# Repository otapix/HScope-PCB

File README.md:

# HScope-PCB
HScope PCB

PCB for 

https://www.martinloren.com/

https://github.com/martinloren/HScope/

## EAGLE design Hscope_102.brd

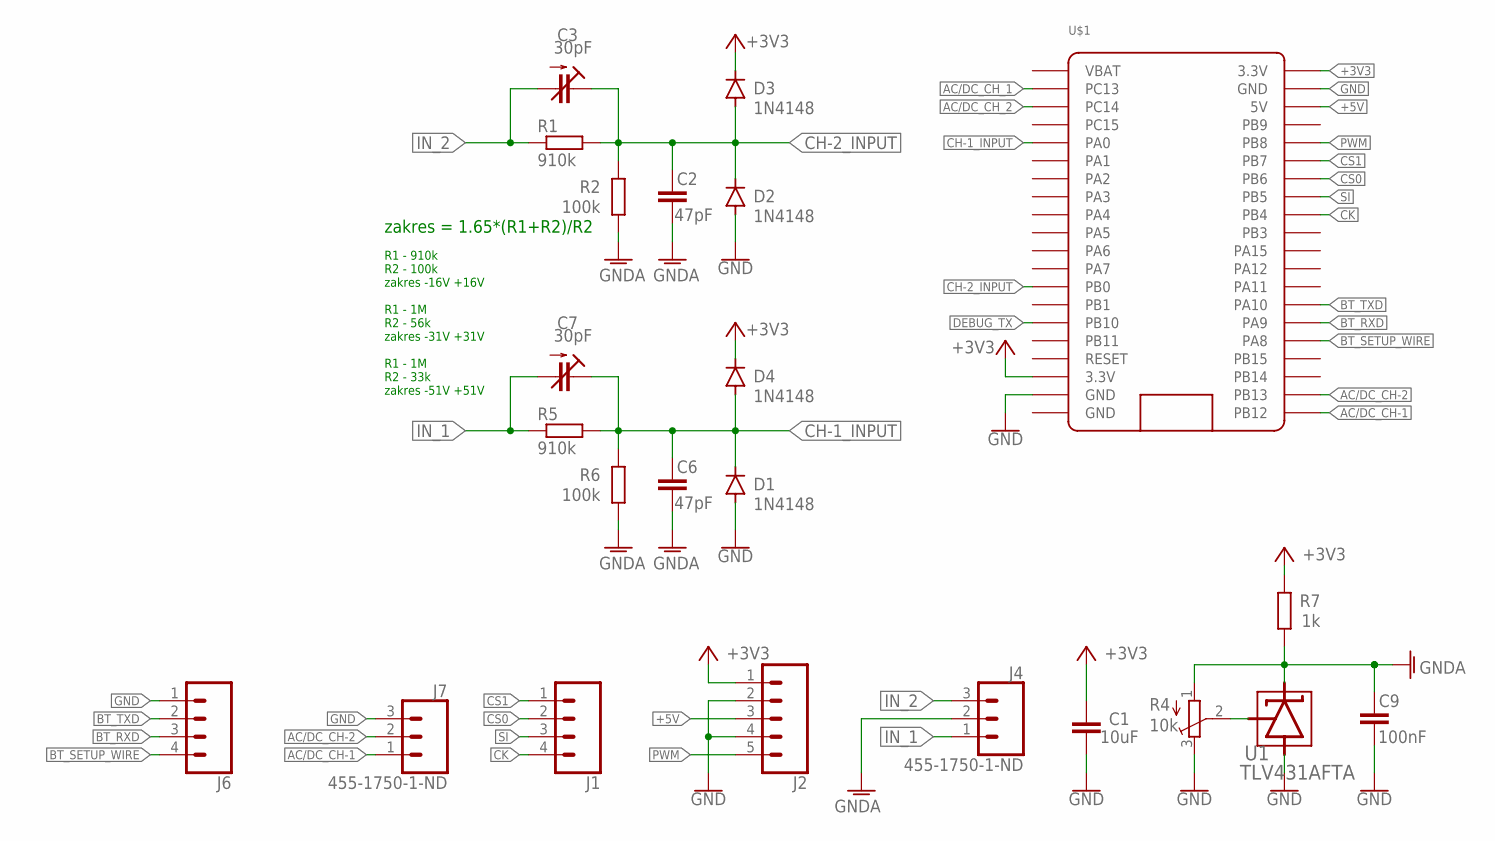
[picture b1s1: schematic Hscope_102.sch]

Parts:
C1: 10uF; C0805
C2, C6: 47pF; C0805
C3, C7: 30pF; CTRIM3018_12
C9: 100nF; C0805
D1, D2, D3, D4: 1N4148; SOD323-W
J1, J6: CONN_04PTH; 1X04
J2: CONN_05; 1X05
J4, J7: 455-1750-1-ND; 1X03
R1, R5: 910k; R0805
R2, R6: 100k; R0805
R4: 10k; SM-42/43A
R7: 1k; R0805
U1: TLV431AFTA; SOT95P237X112-3N
U$1: STM32_BLUEPILL

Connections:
+3V3: C1.2, D3.C, D4.C, J2.1, R7.2, U$1.P$20 (3.3V), U$1.P$23 (3.3V)
+5V: J2.3, U$1.P$18 (5V)
AC/DC_CH-1: J7.1, U$1.P$1 (PB12)
AC/DC_CH-2: J7.2, U$1.P$2 (PB13)
AC/DC_CH_1: U$1.P$39 (PC13)
AC/DC_CH_2: U$1.P$38 (PC14)
BT_RXD: J6.3, U$1.P$6 (PA9)
BT_SETUP_WIRE: J6.4, U$1.P$5 (PA8)
BT_TXD: J6.2, U$1.P$7 (PA10)
CH-1_INPUT: C6.2, C7.+ (E), D1.C, D4.A, R5.2, R6.2, U$1.P$36 (PA0)
CH-2_INPUT: C2.2, C3.+ (E), D2.C, D3.A, R1.2, R2.2, U$1.P$28 (PB0)
CK: J1.4, U$1.P$12 (PB4)
CS0: J1.2, U$1.P$14 (PB6)
CS1: J1.1, U$1.P$15 (PB7)
DEBUG_TX: U$1.P$26 (PB10)
GND: C1.1, C9.1, D1.A, D2.A, J2.2, J2.4, J6.1, J7.3, R4.3 (E), U1.3 (ANODE), U$1.P$19 (GND), U$1.P$21 (GND), U$1.P$22 (GND)
GNDA: C2.1, C6.1, C9.2, J4.2, R2.1, R4.1 (A), R6.1, R7.1, U1.2 (CATHODE)
IN_1: C7.- (A), J4.1, R5.1
IN_2: C3.- (A), J4.3, R1.1
unnamed: R4.2 (S), U1.1 (REF)
PWM: J2.5, U$1.P$16 (PB8)
SI: J1.3, U$1.P$13 (PB5)
VBAT: U$1.P$40 (VBAT)

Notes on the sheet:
R1 - 910k R2 - 100k zakres -16V +16V R1 - 1M R2 - 56k zakres -31V +31V R1 - 1M R2 - 33k zakres -51V +51V
zakres = 1.65*(R1+R2)/R2

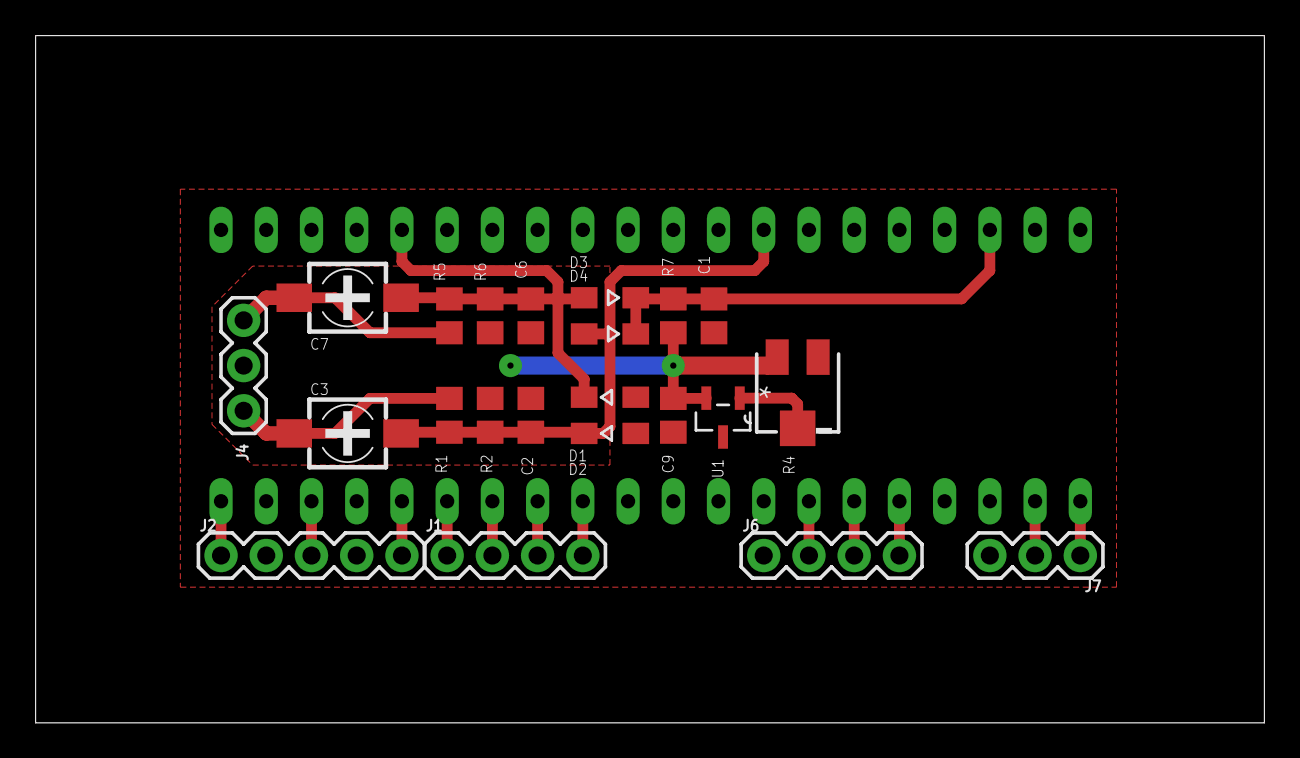
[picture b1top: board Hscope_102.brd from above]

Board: 2 copper layers, 69.0 x 38.6 mm, 23 parts (1 on the bottom side), 19 nets.

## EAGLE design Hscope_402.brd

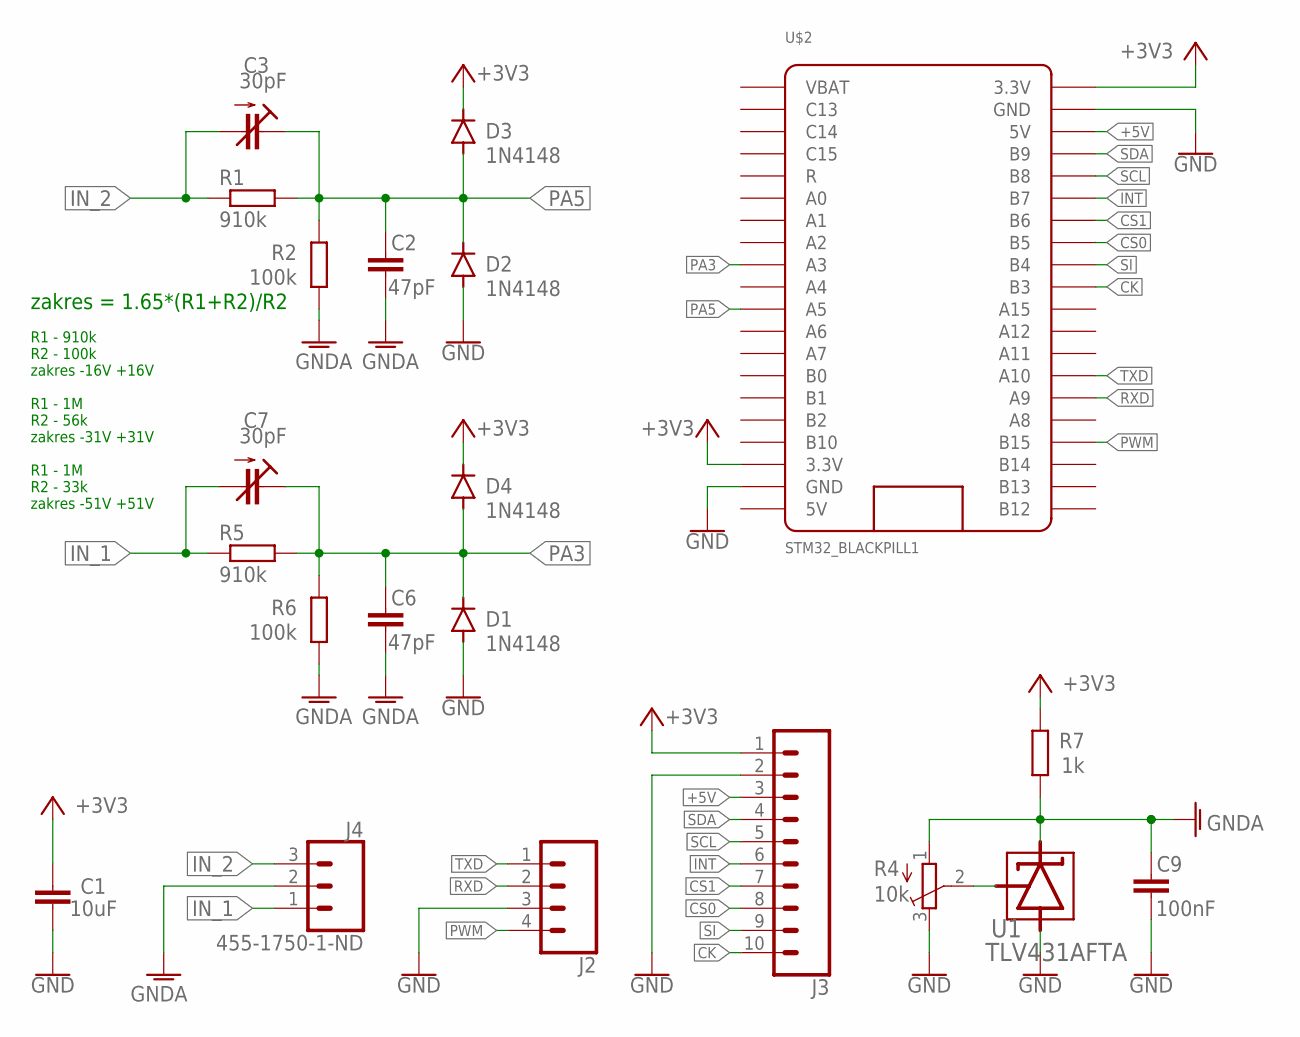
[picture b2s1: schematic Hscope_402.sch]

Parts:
C1: 10uF; C0805
C2, C6: 47pF; C0805
C3, C7: 30pF; CTRIM3018_12
C9: 100nF; C0805
D1, D2, D3, D4: 1N4148; SOD323-W
J2: CONN_04PTH; 1X04
J3: CONN_10"; 1X10
J4: 455-1750-1-ND; 1X03
R1, R5: 910k; R0805
R2, R6: 100k; R0805
R4: 10k; SM-42/43A
R7: 1k; R0805
U1: TLV431AFTA; SOT95P237X112-3N
U$2: STM32_BLACKPILL1; STM32_BLACKPILL

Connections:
5V: U$2.P$21 (5V)
+3V3: C1.2, D3.C, D4.C, J3.1, R7.2, U$2.P$20 (3.3V), U$2.P$23 (3.3V)
+5V: J3.3, U$2.P$18 (5V)
CK: J3.10, U$2.P$11 (B3)
CS0: J3.8, U$2.P$13 (B5)
CS1: J3.7, U$2.P$14 (B6)
GND: C1.1, C9.1, D1.A, D2.A, J2.3, J3.2, R4.3 (E), U1.3 (ANODE), U$2.P$19 (GND), U$2.P$22 (GND)
GNDA: C2.1, C6.1, C9.2, J4.2, R2.1, R4.1 (A), R6.1, R7.1, U1.2 (CATHODE)
INT: J3.6, U$2.P$15 (B7)
IN_1: C7.- (A), J4.1, R5.1
IN_2: C3.- (A), J4.3, R1.1
unnamed: R4.2 (S), U1.1 (REF)
PA3: C6.2, C7.+ (E), D1.C, D4.A, R5.2, R6.2, U$2.P$32 (A3)
PA5: C2.2, C3.+ (E), D2.C, D3.A, R1.2, R2.2, U$2.P$30 (A5)
PWM: J2.4, U$2.P$4 (B15)
RXD: J2.2, U$2.P$6 (A9)
SCL: J3.5, U$2.P$16 (B8)
SDA: J3.4, U$2.P$17 (B9)
SI: J3.9, U$2.P$12 (B4)
TXD: J2.1, U$2.P$7 (A10)
VBAT: U$2.P$40 (VBAT)

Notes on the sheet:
R1 - 910k R2 - 100k zakres -16V +16V R1 - 1M R2 - 56k zakres -31V +31V R1 - 1M R2 - 33k zakres -51V +51V
zakres = 1.65*(R1+R2)/R2

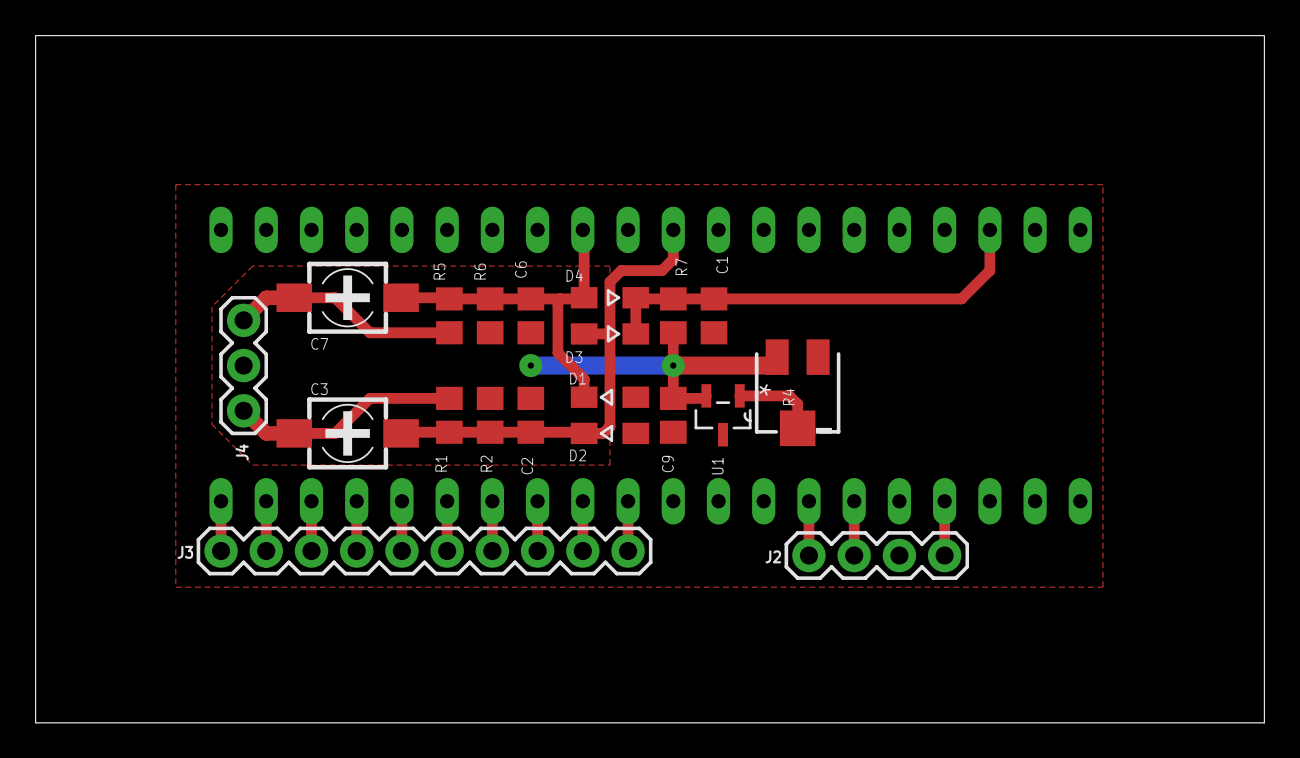
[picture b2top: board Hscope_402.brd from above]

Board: 2 copper layers, 69.0 x 38.6 mm, 21 parts (1 on the bottom side), 19 nets.

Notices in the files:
parts and their libraries:
SparkFun-Connectors: Licensing: Creative Commons ShareAlike 4.0 International - https://creativecommons.org/licenses/by-sa/4.0
